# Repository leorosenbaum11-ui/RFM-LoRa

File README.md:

# RF-Messager-Project
Long range telemetry and communication through LoRa chip WIO-LR2021
PCB in 3d printed case with Keyboard, Screen, 2 SMA Antenna Ports, and GPS FL Antenna port

Part Models (more detailed BOM in files):
Microcontroller: Adafruit Feather ESP32-S3
Pin Extender: MCU23S17
Transciever: Seeed WIO-LR2021
Keyboard Driver: STM32F042CFU(x)
Keyboard: Solderparty Keebdeck Keyboard_6R13C
GPS: Adafruit Ultimate GPS MTK3339
Sensors: TI TMP-100 Temperature, MAX17048 Battery, BME280 Pressure Humidity
Compass: LSM303AGR Compass Accelerometer
Screen: ILI9341 Non-Touch

Program:
upload bbq10 firmware to stm32 and configure
upload my firmware

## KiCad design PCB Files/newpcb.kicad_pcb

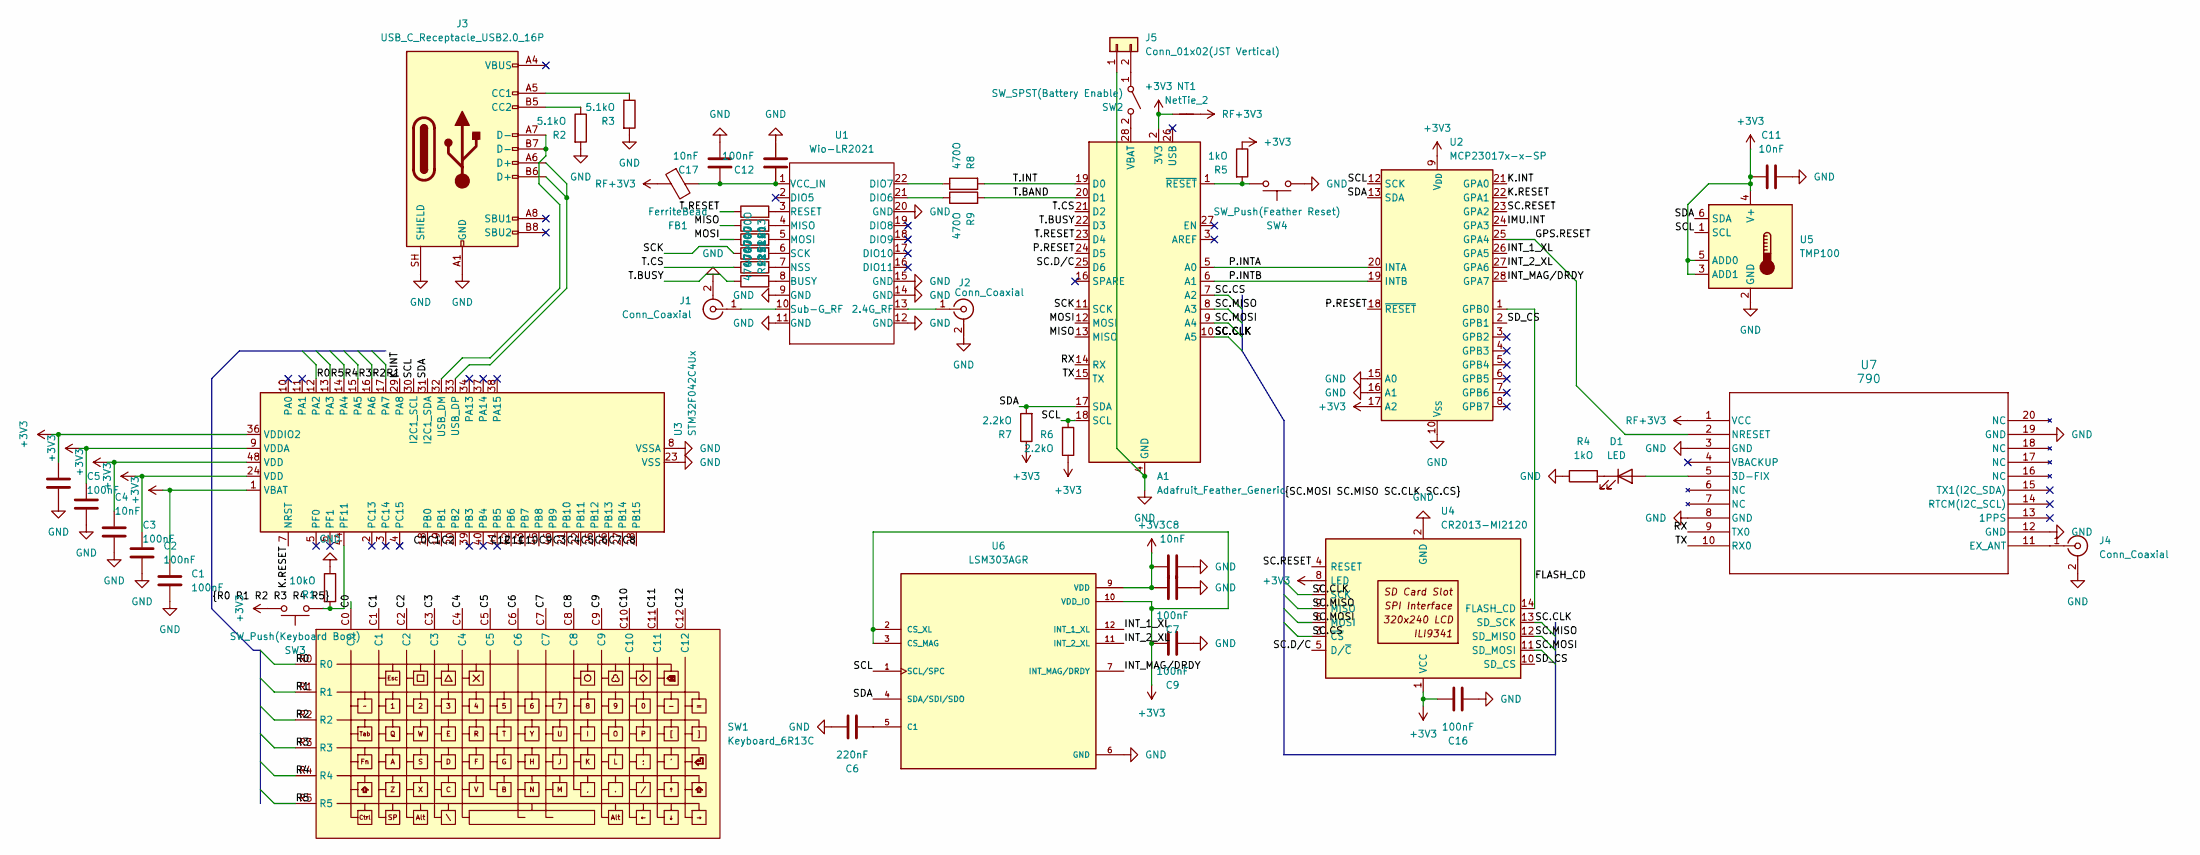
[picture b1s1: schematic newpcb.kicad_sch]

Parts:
A1: Adafruit_Feather_Generic; Adafruit_Feather
C1, C2, C3, C5, C7, C9, C12, C16: 100nF; C_0603_1608Metric_Pad1.08x0.95mm_HandSolder
C4, C8, C11, C17: 10nF; C_0603_1608Metric_Pad1.08x0.95mm_HandSolder
C6: 220nF; C_0603_1608Metric_Pad1.08x0.95mm_HandSolder
D1: LED; LED_0603_1608Metric_Pad1.05x0.95mm_HandSolder
FB1: FerriteBead; L_0603_1608Metric_Pad1.05x0.95mm_HandSolder
J1, J2: Conn_Coaxial; SMA_Molex_73251-1153_EdgeMount_Horizontal
J3: USB_C_Receptacle_USB2.0_16P; USB_C_Receptacle_HRO_TYPE-C-31-M-12
J4: Conn_Coaxial; U.FL_Molex_MCRF_73412-0110_Vertical
J5: Conn_01x02(JST Vertical); JST_PH_B2B-PH-K_1x02_P2.00mm_Vertical
NT1: NetTie_2; NetTie-2_SMD_Pad2.0mm
R1: 10kO; R_0603_1608Metric_Pad0.98x0.95mm_HandSolder
R2, R3: 5.1kO; R_0603_1608Metric_Pad0.98x0.95mm_HandSolder
R4, R5: 1kO; R_0603_1608Metric_Pad0.98x0.95mm_HandSolder
R6, R7: 2.2kO; R_0603_1608Metric_Pad0.98x0.95mm_HandSolder
R8, R9, R10, R11, R12, R13, R14, R15: 470O; R_0603_1608Metric_Pad0.98x0.95mm_HandSolder
SW1: Keyboard_6R13C
SW2: SW_SPST(Battery Enable); SW_DIP_SPSTx01_Slide_6.7x4.1mm_W6.73mm_P2.54mm_LowProfile_J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
SW3: SW_Push(Keyboard Boot); SW_Push_1TS009xxxx-xxxx-xxxx_6x6x5mm
SW4: SW_Push(Feather Reset); SW_Push_1TS009xxxx-xxxx-xxxx_6x6x5mm
U1: Wio-LR2021; Wio-LR2021_V1
U2: MCP23017x-x-SP; DIP-28_W7.62mm
U3: STM32F042C4Ux; QFN-48-1EP_7x7mm_P0.5mm_EP5.6x5.6mm
U4: CR2013-MI2120
U5: TMP100; SOT-23-6
U6: LSM303AGR; PQFN50P200X200X100-12N; PARTREV 10
U7: 790; PA1616S_ADA

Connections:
+3V3: A1.2 (3V3), C1.1, C2.1, C3.1, C4.1, C5.1, C7.1, C8.1, C9.1, C11.1, C16.1, NT1.1, R5.1, R6.1, R7.1, SW3.1, U2.9 (V_{DD}), U2.17 (A2), U3.1 (VBAT), U3.9 (VDDA), U3.24 (VDD), U3.36 (VDDIO2), U3.48 (VDD), U4.1 (VCC), U4.8 (LED), U5.3 (ADD1), U5.4 (V+), U5.5 (ADD0), U6.2 (CS_XL), U6.3 (CS_MAG), U6.9 (VDD), U6.10 (VDD_IO)
/C0: SW1.C0, U3.18 (PB0)
/C1: SW1.C1, U3.19 (PB1)
/C2: SW1.C2, U3.20 (PB2)
/C3: SW1.C3, U3.21 (PB10)
/C4: SW1.C4, U3.22 (PB11)
/C5: SW1.C5, U3.25 (PB12)
/C6: SW1.C6, U3.26 (PB13)
/C7: SW1.C7, U3.27 (PB14)
/C8: SW1.C8, U3.28 (PB15)
/C9: SW1.C9, U3.46 (PB9)
/C10: SW1.C10, U3.45 (PB8)
/C11: SW1.C11, U3.43 (PB7)
/C12: SW1.C12, U3.42 (PB6)
/FLASH_CD: U2.1 (GPB0), U4.14 (FLASH_CD)
/GPS.RESET: U2.25 (GPA4), U7.2 (NRESET)
/IMU.INT: U2.24 (GPA3)
/INT_1_XL: U2.26 (GPA5), U6.12 (INT_1_XL)
/INT_2_XL: U2.27 (GPA6), U6.11 (INT_2_XL)
/INT_MAG/DRDY: U2.28 (GPA7), U6.7 (INT_MAG/DRDY)
/K.INT: U2.21 (GPA0), U3.29 (PA8)
/K.RESET: U2.22 (GPA1), U3.7 (NRST)
/MISO: A1.13 (MISO), R11.1
/MOSI: A1.12 (MOSI), R12.1
/P.INTA: A1.5 (A0), U2.20 (INTA)
/P.INTB: A1.6 (A1), U2.19 (INTB)
/P.RESET: A1.24 (D5), U2.18 (~RESET)
/R0: SW1.R0, U3.12 (PA2)
/R1: SW1.R1, U3.17 (PA7)
/R2: SW1.R2, U3.16 (PA6)
/R3: SW1.R3, U3.15 (PA5)
/R4: SW1.R4, U3.14 (PA4)
/R5: SW1.R5, U3.13 (PA3)
/RX: A1.14 (RX), U7.9 (TX0)
/SC.CLK: A1.10 (A5), U4.7 (SCK), U4.13 (SD_SCK)
/SC.CS: A1.7 (A2), U4.3 (~CS)
/SC.D/C: A1.25 (D6), U4.5 (D/~C)
/SC.MISO: A1.8 (A3), U4.9 (MISO), U4.12 (SD_MISO)
/SC.MOSI: A1.9 (A4), U4.6 (MOSI), U4.11 (SD_MOSI)
/SC.RESET: U2.23 (GPA2), U4.4 (RESET)
/SCK: A1.11 (SCK), R13.1
/SCL: A1.18 (SCL), R6.2, U2.12 (SCK), U3.30 (I2C1_SCL), U5.1 (SCL), U6.1 (SCL/SPC)
/SDA: A1.17 (SDA), R7.2, U2.13 (SDA), U3.31 (I2C1_SDA), U5.6 (SDA), U6.4 (SDA/SDI/SDO)
/SD_CS: U2.2 (GPB1), U4.10 (SD_CS)
/T.BAND: A1.20 (D1), R9.2
/T.BUSY: A1.22 (D3), R15.1
/T.CS: A1.21 (D2), R14.1
/T.INT: A1.19 (D0), R8.2
/T.RESET: A1.23 (D4), R10.1
/TX: A1.15 (TX), U7.10 (RX0)
GND: A1.4 (GND), C1.2, C2.2, C3.2, C4.2, C5.2, C6.1, C7.2, C8.2, C9.2, C11.2, C12.2, C16.2, C17.2, J1.2 (Ext), J2.2 (Ext), J3.A1 (GND), J3.A12 (GND), J3.B1 (GND), J3.B12 (GND), J3.SH (SHIELD), J4.2 (Ext), J5.1, R1.1, R2.2, R3.2, R4.1, SW4.2, U1.9 (GND), U1.11 (GND), U1.12 (GND), U1.14 (GND), U1.15 (GND), U1.20 (GND), U2.10 (V_{SS}), U2.15 (A0), U2.16 (A1), U3.8 (VSSA), U3.23 (VSS), U3.35 (VSS), U3.47 (VSS), U3.49 (VSS), U4.2 (GND), U5.2 (GND), U6.6 (GND), U6.8 (GND), U7.3 (GND), U7.8 (GND), U7.12 (GND), U7.19 (GND)
unnamed: A1.28 (VBAT), SW2.2 (B)
unnamed: A1.1 (~RESET), R5.2, SW4.1
unnamed: D1.2 (A), U7.5 (3D-FIX)
unnamed: D1.1 (K), R4.2
unnamed: J1.1 (In), U1.10 (Sub-G_RF)
unnamed: J2.1 (In), U1.13 (2.4G_RF)
unnamed: J3.A5 (CC1), R3.1
unnamed: J3.B5 (CC2), R2.1
unnamed: J4.1 (In), U7.11 (EX_ANT)
unnamed: J5.2, SW2.1 (A)
unnamed: R15.2, U1.8 (BUSY)
unnamed: R9.1, U1.21 (DIO6)
unnamed: R8.1, U1.22 (DIO7)
unnamed: R11.2, U1.4 (MISO)
unnamed: R12.2, U1.5 (MOSI)
unnamed: R14.2, U1.7 (NSS)
unnamed: R10.2, U1.3 (RESET)
unnamed: R13.2, U1.6 (SCK)
unnamed: C12.1, C17.1, FB1.2, U1.1 (VCC_IN)
unnamed: J3.A7 (D-), J3.B7 (D-), U3.32 (USB_DM)
unnamed: J3.A6 (D+), J3.B6 (D+), U3.33 (USB_DP)
unnamed: R1.2, SW3.2, U3.44 (PF11)
unnamed: C6.2, U6.5 (C1)
RF+3V3: FB1.1, NT1.2, U7.1 (VCC)

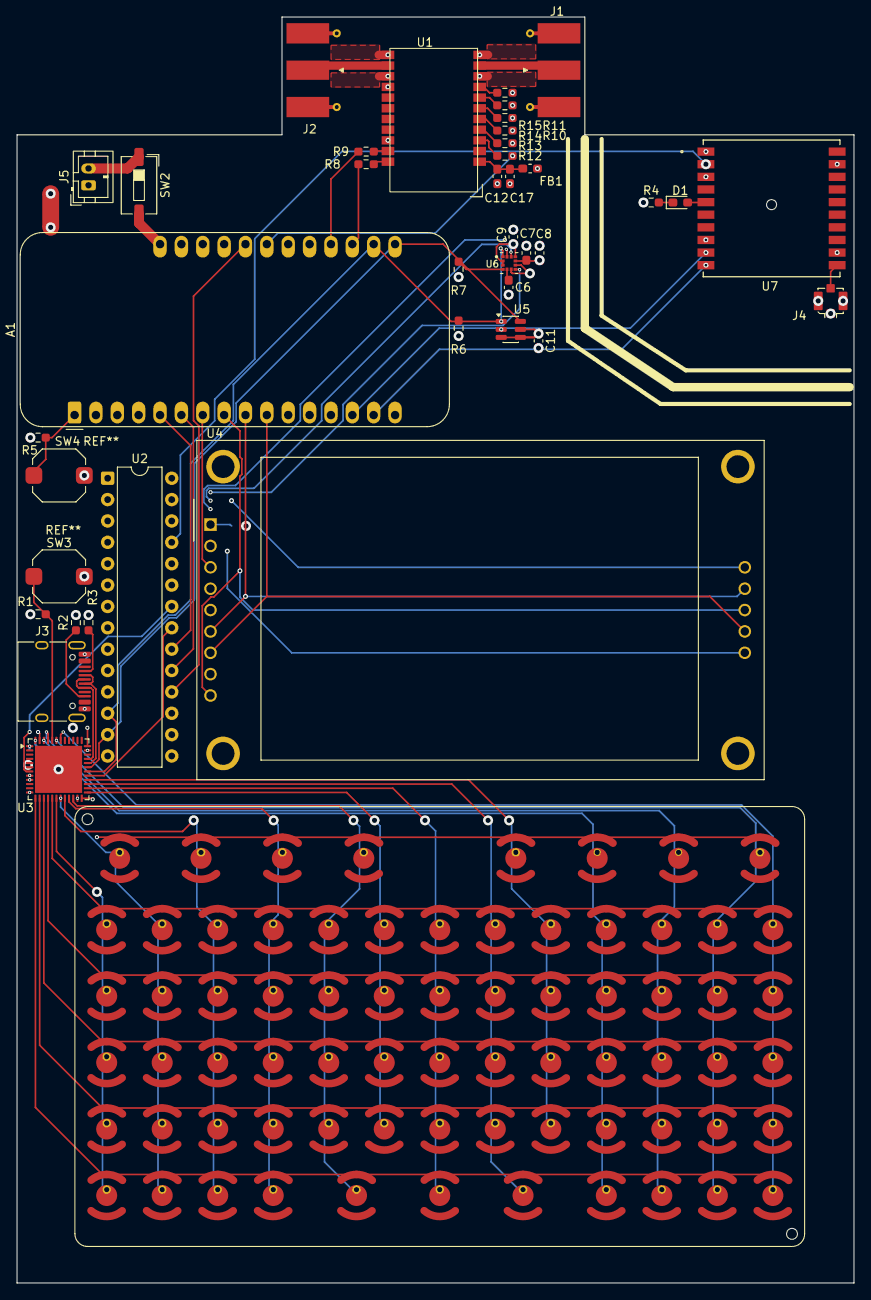
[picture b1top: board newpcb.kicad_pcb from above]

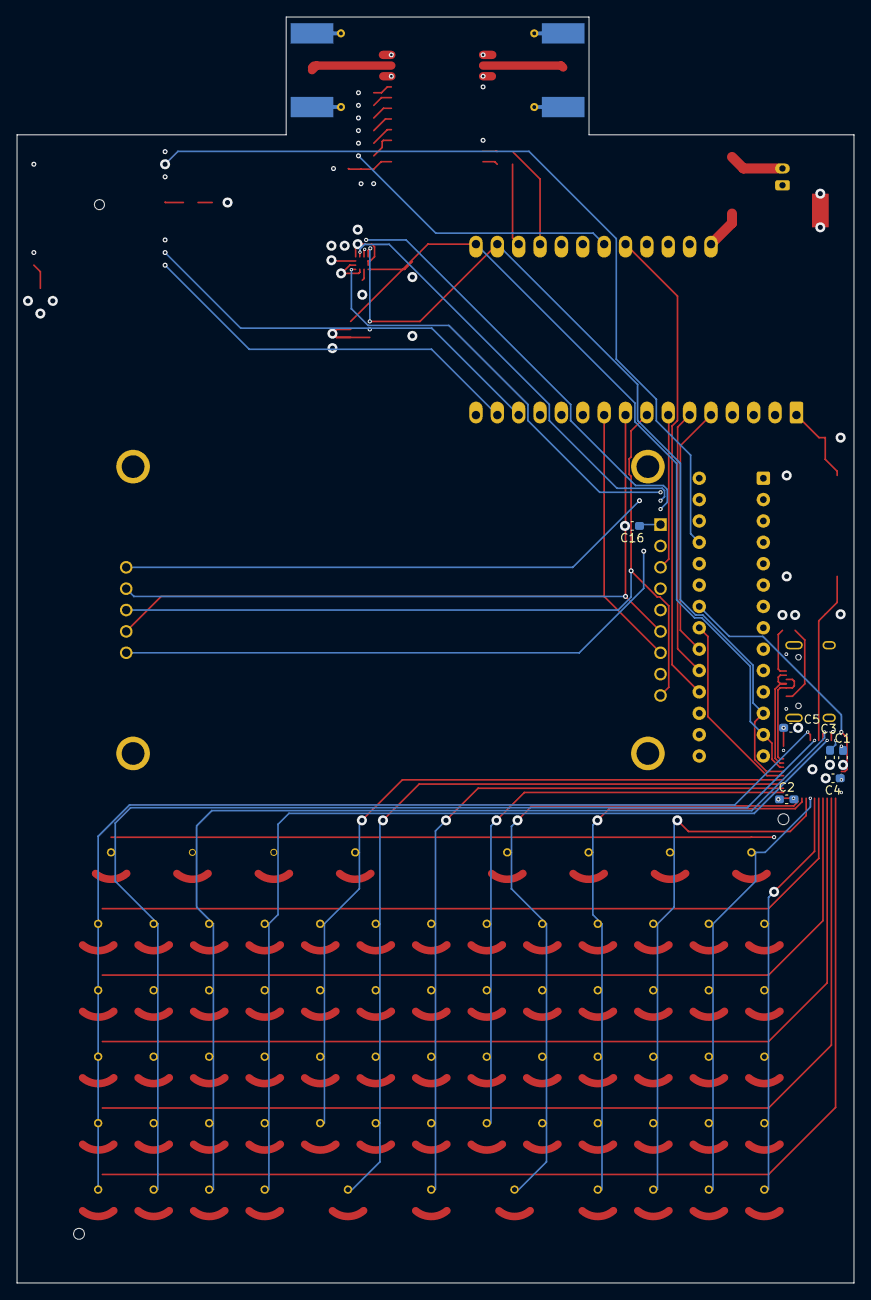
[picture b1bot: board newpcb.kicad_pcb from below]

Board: 4 copper layers, 99.5 x 150.5 mm, 48 parts (6 on the bottom side), 74 nets.
